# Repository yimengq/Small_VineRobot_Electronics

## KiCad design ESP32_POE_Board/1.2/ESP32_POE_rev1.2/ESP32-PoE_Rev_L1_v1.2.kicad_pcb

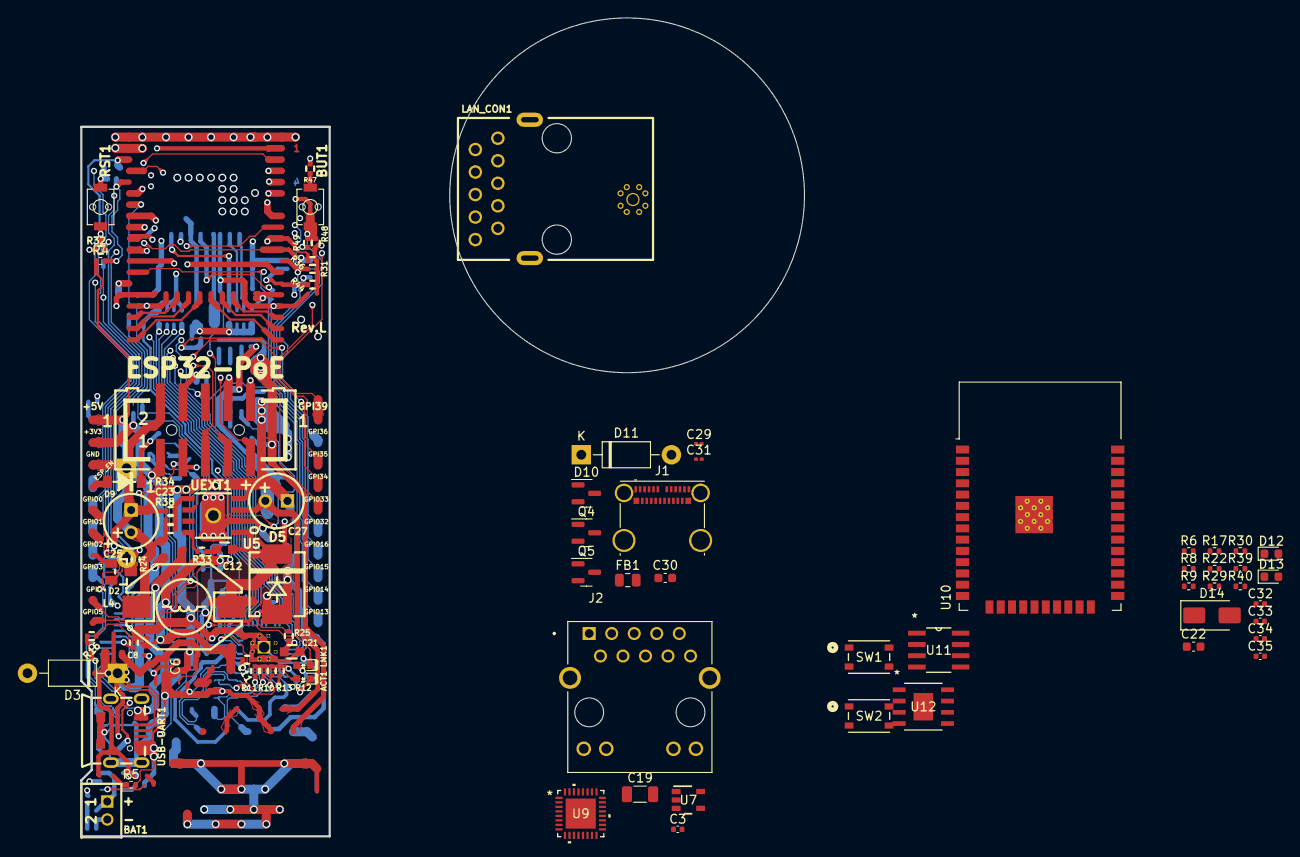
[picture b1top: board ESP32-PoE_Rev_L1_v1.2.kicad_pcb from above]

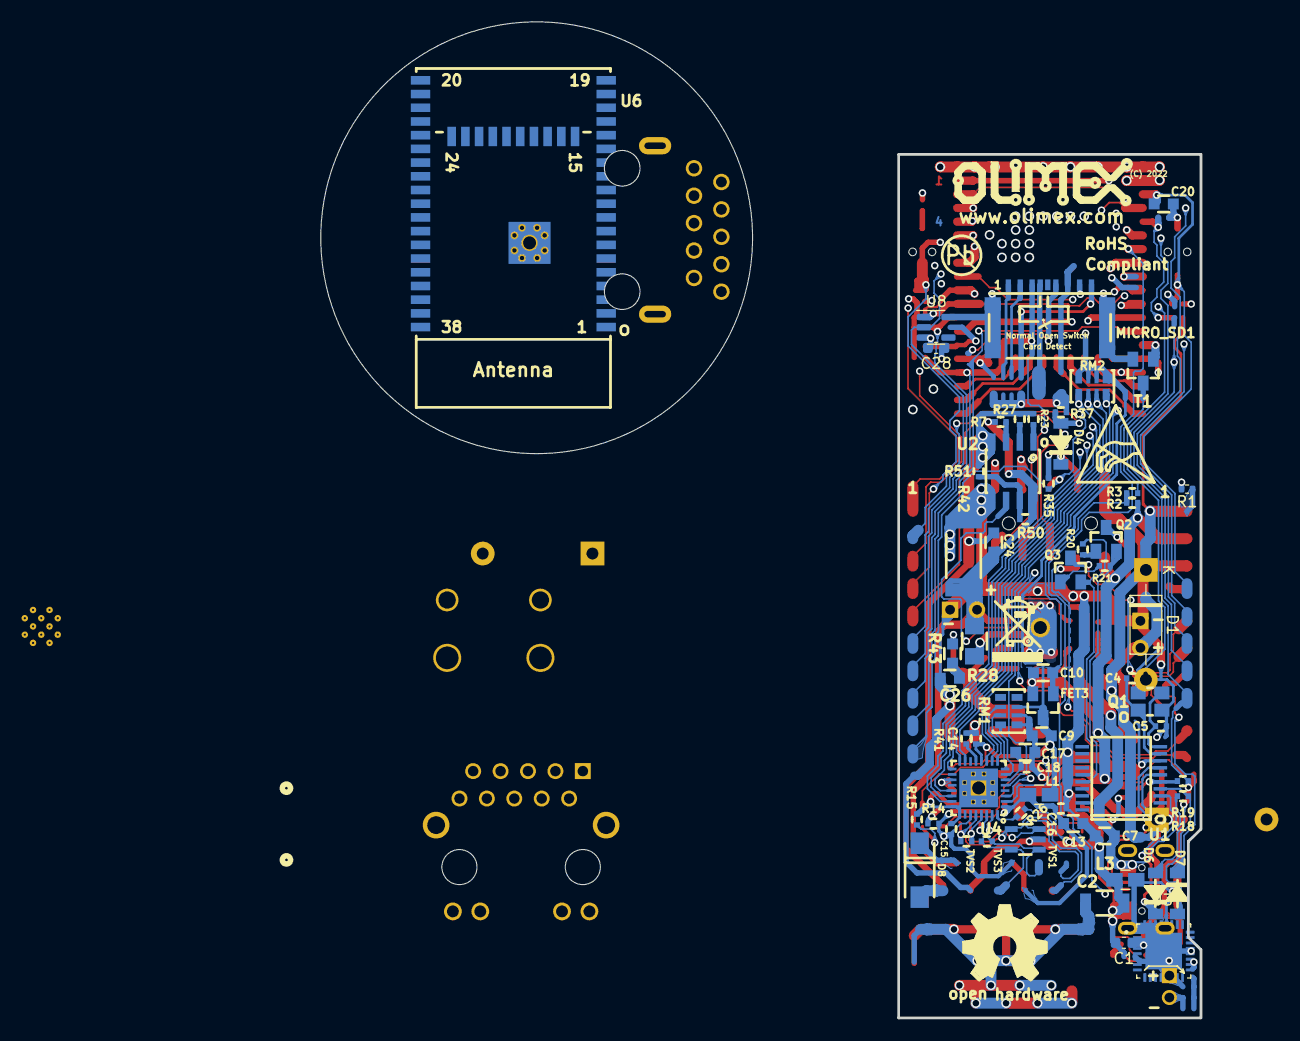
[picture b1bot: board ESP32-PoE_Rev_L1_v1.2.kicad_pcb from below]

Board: 4 copper layers, 81.5 x 92.3 mm, 144 parts (67 on the bottom side), 104 nets.

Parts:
ACT1: LED/YELLOW/0603; LED_0603_KA
BAT1: DW02S; LIPO_BAT_VERTICAL_DW02S
BUT1: IT1185AU2; IT1185AU2_V2
C1, C28, C30: 10uF; C_0603_1608Metric
C2: 1nF/2000V/10%/X7R/C1206; C_1206_5MIL_DWS_ISO
C3, C32, C34, C35: 100nF; C_0402_1005Metric
C4, C5: 27pF/50V/5%/C0G/C0402; C_0402_5MIL_DWS
C6, C29, C31: 1uF; C_0201_0603Metric
C7, C9, C10, C13: 22uF/6.3V/20%/X5R/C0603; C_0603_5MIL_DWS
C8, C11, C14, C15, C16, C18: 100nF/16V/10%/X7R/C0402; C_0402_5MIL_DWS
C12, C24: 100nF/100V/10%/X7R/C0603; C_0603_5MIL_DWS
C17: 2.2uF/6.3V/10%/X5R/C0603; C_0603_5MIL_DWS
C19: 1nF; C_1206_3216Metric
C20: 1uF/10V/20%/X5R/C0603; C_0603_5MIL_DWS
C21: NA(10uF/6.3V/20%/X5R/C0603); C_0603_5MIL_DWS
C22: 22uF; C_0603_1608Metric
C23: 12pF/50V/5%/COG/C0402; C_0402_5MIL_DWS
C25: 470uF/10V/20%/Low_ESR/RM2.5/6.0x11mm; CPOL-RM2.5mm_6.3x11mm_PTH
C26: NA(220pF/100V/C0603); C_0603_5MIL_DWS
C27: 15uF/100V/20%/RM2.5/6.3x11mm(Farnell:1281844); CPOL-RM2.5mm_6.3x11mm_PTH
C33: 2.2uF; C_0402_1005Metric
D1, D3, D11: 1N5819; D_DO-41_SOD81_P10.16mm_Horizontal
D2: BAT54C(SOT23-3); SOT23-3
D4, D6, D7, D9: 1N5819S4(SOD-123); SOD-123_1C-2A_KA
D5: SS510/100V/5A/0.85V/DO214AB(SMC); DO214AB(SMC)_1(K)-2(A)
D8: SMAJ58A/SMA; SMA-KA
D10: BAT54C; SOT-23
D12, D13: LED; LED_0603_1608Metric
D14: SMAJ58A; D_SMA
FB1: 600R-2A; C_0805_2012Metric
FET3: WPM2015-3/TR; SOT23
J1: USB_C_Receptacle; USB_C_Receptacle_Molex_105450-0101-L
J2: SI-46020-F; BEL_SI-46020-F
L1, L3: FB0805/600R/2A; L_0805_5MIL_DWS
L4: 33uH/2.1A/DCR=0.1R/20%/DBS135(PD3316MT330); DBS135
LAN_CON1: RJP-003TC1(LPJ4112CNL)
LNK1: LED/GREEN/0603; LED_0603_KA
Logo_OSHW: LOGO_OPENHARDWARE_8x8
Logo_Olimex: OLIMEX_LOGO_TB
MICRO_SD1: TFC-9P-1.7H(ATFFS150A01BR016); uSD(TFC-9P-1.xH(ATFFS150A01BR016))
Q1: Q12MHz/20pF/10ppm/4P/3.2x2.5mm; TSX-3.2x2.5mm_GND(3)
Q2, Q3: BC817-40(SOT23); SOT23
Q4, Q5: BC817; SOT-23
R1, R4: 1k; R_0402_1005Metric
R2, R18, R19, R25, R32, R36, R37, R48: 10k/R0402; R_0402_5MIL_DWS
R3, R20, R21: 1k/R0402; R_0402_5MIL_DWS
R5: 220; R_0402_1005Metric
R6, R8, R9, R17: 2.2k; R_0402_1005Metric
R7: 24.9k/1%/R0402; R_0402_5MIL_DWS
R10, R11, R12, R13: 49.9R/1%/R0402; R_0402_5MIL_DWS
R14, R15, R31, R35, R41: 2.2k/R0402; R_0402_5MIL_DWS
R16, R51: NA(10k/R0402); R_0402_5MIL_DWS
R22: 130k; R_0402_1005Metric
R23: 180k/1%/R0402; R_0402_5MIL_DWS
R24, R47: 220R/R0402; R_0402_5MIL_DWS
R26: 12.1k/1%/R0402; R_0402_5MIL_DWS
R27: 4.42k/1%/1/16W/R0402; R_0402_5MIL_DWS
R28: 0.03R/1%/R1206; R_1206_5MIL_DWS
R29, R30: 10k; R_0402_1005Metric
R33: 4.7R/R0402; R_0402_5MIL_DWS
R34: 5.23k/1%/R0402; R_0402_5MIL_DWS
R38: 30.1k/1%/R0402; R_0402_5MIL_DWS
R39: 4.42k; R_0402_1005Metric
R40: 24.9k; R_0402_1005Metric
R42: 4.7k/R2512; R_2512_MM_DWS
R43: NA(22R/R0603); R_0603_5MIL_DWS
R44, R49: NA/R0402; R_0402_5MIL_DWS
R50: NA(130k/R0402); R_0402_5MIL_DWS
RM1, RM2: RA1206_(4X0603)_4B8_2.2k; R_MATRIX_4
RST1: IT1185AU2; IT1185AU2_V2
SW1, SW2: PTS815 SJM 250 SMTR LFS; SW4_PTS815 SJM 250 SMTR LFS_CNK
Sign_Antistatic: Val**; LOGO_ANTISTATIC_1
Sign_PB-Free: LOGO_PBFREE
Sign_RecycleBin: LOGO_RECYCLEBIN_1
T1: LMUN2211LT1G(SOT-23); SOT23
TVS1: ESDS314DBVR(SOT-23-5); SOT-23-5
TVS2, TVS3: NA(GG0402052R542P); D_0402_5MIL_DWS
U1: CH340T(SSOP20W); SSOP-20W
U2: TPS2375D(SO-8); SOIC-8_1.75mm
U3: FT232RQ; QFN50P500X500X90-33N
U4: LAN8710A-EZC(QFN32); QFN32_EP(33)_5.00x5.00x0.90mm_Pitch_0.50mm
U5: TX4138(ESOIC-8); ESOIC-8
U6: ESP32-WROVER-E; ESP32-WROVER(WROOM)-UNIVERSAL_MODULE
U7: ESDS314DBVR; DBV0005A_N
U8: MIC5504-3.3YM5; SOT-23-5
U9: LAN8710A-EZC; QFN32_5X5MC_MCH
U10: ESP32-WROOM-32
U11: TPS2375D; D8
U12: TX4138; ESOIC8_XDS
UEXT1: P-B-V-10-LF; GBH-254-SMT-10
USB-UART1: MISB-SWMM-5B-LF(USB_MICRO); USB-MICRO_MISB-SWMM-5B_LF

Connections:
+3.3V: C10.1, C30.1, C31.1, FET3.2, R2.1, R16.2, R31.1, R32.1, R35.1, R36.1, R37.1, R44.2, R48.1, U6.2 (VDD33(3V3)), U8.5 (VOUT), UEXT1.1
+3.3VLAN: C9.1, C14.1, FET3.3, L1.1, R25.2, RM1.3.1, RM2.1.1, RM2.2.1, RM2.3.1, RM2.4.1, U4.12 (VDDIO)
+5VP: C23.1, C25.1 (+), C28.1, C29.1, L4.2, R38.1, U8.1 (VIN), U8.3 (EN)
/+5V_USB: C7.1, R18.1, U1.19 (VCC), USB-UART1.1 (VBUS)
/D_Com: D2.3 (CC), R24.2, R49.2
/GPI34\BUT1: BUT1.1, R48.2, R49.1, U6.6 (GPI34/ADC1_CH6/RTC_GPIO4)
/GPI36\U1RXD: D4.2 (A), R37.2, U6.4 (GPI36/SENSOR_VP/ADC1_CH0/RTC_GPIO0)
/GPIO1\U0TXD: D7.1 (K), U6.35 (GPIO1/U0TXD/CLK_OUT3/EMAC_RXD2)
/GPIO3\U0RXD: D6.2 (A), R16.1, R19.2, U6.34 (GPIO3/U0RXD/CLK_OUT2)
/GPIO4\U1TXD: U6.26 (GPIO4/ADC2_CH0/TOUCH0/RTC_GPIO10/HSPIHD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), UEXT1.3
/GPIO5\SPI_CS: R36.2, U6.29 (GPIO5/VSPICS0/HS1_DATA6/EMAC_RX_CLK), UEXT1.10
/GPIO12\PHY_PWR: T1.1 (B), U6.14 (GPIO12/ADC2_CH5/TOUCH5/RTC_GPIO15/MTDI/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)
/GPIO13\I2C-SDA: R35.2, U6.16 (GPIO13/ADC2_CH4/TOUCH4/RTC_GPIO14/MTCK/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), UEXT1.6
/GPIO14\HS2_CLK: U6.13 (GPIO14/ADC2_CH6/TOUCH6/RTC_GPIO16/MTMS/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), UEXT1.9
/GPIO15\HS2_CMD: MICRO_SD1.3 (CMD/DI), U6.23 (GPIO15/ADC2_CH3/TOUCH3/MTDO/HSPICS0/RTC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), UEXT1.7
/GPIO16\I2C-SCL: R31.2, U6.27 (NC(GPIO16/HS1_DATA4/U2RXD/EMAC_CLK_OUT)), UEXT1.5
/GPIO17\EMAC_CLK_OUT_180: U4.5 (XTAL1/CLKIN), U6.28 (NC(GPIO17/HS1_DATA5/U2TXD/EMAC_CLK_OUT_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)
/GPIO18\MDIO(RMII): RM2.4.2, U4.16 (MDIO), U6.30 (GPIO18/VSPICLK/HS1_DATA7)
/GPIO19\EMAC_TXD0(RMII): U4.22 (TXD0), U6.31 (GPIO19/VSPIQ/U0CTS/EMAC_TXD0)
/GPIO21\EMAC_TX_EN(RMII): U4.21 (TXEN), U6.33 (GPIO21/VSPIHD/EMAC_TX_EN)
/GPIO22\EMAC_TXD1(RMII): U4.23 (TXD1), U6.36 (GPIO22/VSPIWP/U0RTS/EMAC_TXD1)
/GPIO23\MDC(RMII): U4.17 (MDC), U6.37 (GPIO23/VSPID/HS1_STROBE)
/GPIO25\EMAC_RXD0(RMII): RM2.2.2, U4.11 (RXD0/MODE0), U6.10 (GPIO25/DAC_1/ADC2_CH8/RTC_GPIO6/EMAC_RX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)
/GPIO26\EMAC_RXD1(RMII): RM2.1.2, U4.10 (RXD1/MODE1), U6.11 (GPIO26/DAC_2/ADC2_CH9/RTC_GPIO7/EMAC_RX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)
/GPIO27\EMAC_RX_CRS_DV: RM2.3.2, U4.15 (COL/CRS_DV/MODE2), U6.12 (GPIO27/ADC2_CH7/TOUCH7/RTC_GPIO17/EMAC_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)
ESP_EN: C20.1, D9.2 (A), D11.2 (A), R32.2, RST1.1, U6.3 (EN)
GND: BAT1.2, C1.2, C2.1, C3.1, C4.2, C5.2, C6.2, C7.2, C8.2, C9.2, C11.2, C13.2, C14.2, C15.2, C16.2, C17.2, C18.2, C19.1, C20.2, C21.1, C22.2, C25.2 (-), C26.2, C27.2 (-), C28.2, C29.2, C30.2, C31.2, C32.2, C33.2, C34.2, D5.2 (A), FB1.2, J2.7, L3.2, LAN_CON1.7 (GND/NC), LAN_CON1.8 (NC/GND), MICRO_SD1.6 (GND), MICRO_SD1.CH1 (Card_Housing), Q1.3 (case), R8.2, R15.2, R26.2, R34.2, R41.1, R42.2, R47.2, RM1.1.1, RM1.2.1, RST1.2, T1.2 (E), TVS1.2 (GND), U1.8 (GND), U2.5 (RTN), U4.24 (TXD2), U4.25 (TXD3), U4.33 (GND), U5.4 (GND), U6.1 (GND), U6.15 (GND), U6.38 (GND), U6.39 (THERMAL_PAD), U7.2 (GND), U8.2 (GND), U11.5 (RTN), UEXT1.2, USB-UART1.5 (GND)
GPIO0: D2.2 (A2), D10.1, R44.1, U6.25 (GPIO0/ADC2_CH1/TOUCH1/RTC_GPIO11/CLK_OU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)
GPIO2\HS2_DATA0: D2.1 (A1), D10.2, U6.24 (GPIO2/ADC2_CH2/TOUCH2/RTC_GPIO12/HSPIWP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), UEXT1.8
GPIO18/MDIO(RMII): R17.2, U9.16 (MDIO)
GPIO27/EMAC_RX_CRS_DV: R9.2, U9.15 (COL/CRS_DV/*MODE2)
unnamed: ACT1.2 (A), U4.3 (LED1/REGOFF)
unnamed: ACT1.1 (K), R15.1
unnamed: BUT1.2, R47.1
unnamed: C10.2, FET3.1, R2.2, R3.1
unnamed: C12.2, R33.2
unnamed: C19.2, J2.S1 (SHIELD), J2.S2 (SHIELD)
unnamed: C26.1, R43.1
unnamed: D1.1 (K), U3.30 (TXD)
unnamed: D3.2 (A), U3.2 (RXD)
unnamed: D4.1 (K), UEXT1.4
unnamed: C12.1, D5.1 (K), L4.1, R43.2, U5.1 (SW)
unnamed: D6.1 (K), U1.3 (TXD)
unnamed: D7.2 (A), R18.2, U1.4 (RXD)
unnamed: D9.1 (K), Q2.3 (C)
unnamed: D10.3, R5.2
unnamed: D11.1 (K), Q4.3 (C)
unnamed: D12.2 (A), R6.1
unnamed: D12.1 (K), U9.2 (LED2/*NINTSEL)
unnamed: D13.2 (A), U9.3 (LED1/*REGOFF)
unnamed: D13.1 (K), R8.1
unnamed: L3.1, USB-UART1.0
unnamed: C11.1, C13.1, C15.1, C16.1, L1.2, LAN_CON1.4 (TCT), LAN_CON1.5 (RCT), R10.1, R11.1, R12.1, R13.1, R14.1, U4.1 (VDD2A), U4.27 (VDD1A)
unnamed: C2.2, LAN_CON1.0 (Shield)
unnamed: LNK1.2 (A), R14.2
unnamed: LNK1.1 (K), U4.2 (LED2/NINTSEL)
unnamed: Q2.1 (B), R20.2
unnamed: Q2.2 (E), R21.1, U1.16 (RTS#)
unnamed: Q3.1 (B), R21.2
unnamed: Q3.3 (C), R24.1
unnamed: Q3.2 (E), R20.1, U1.15 (DTR#)
unnamed: Q4.1 (B), R1.2
unnamed: Q4.2 (E), R4.1, U3.32 (~RTS)
unnamed: Q5.1 (B), R4.2
unnamed: Q5.3 (C), R1.1, U3.31 (~DTR)
unnamed: Q5.2 (E), R5.1
unnamed: R28.1, U5.2 (ILIM), U5.9 (ILIM)
unnamed: R3.2, T1.3 (C)
unnamed: U1.6 (UD+), USB-UART1.3 (D+)
unnamed: U1.7 (UD-), USB-UART1.2 (D-)
unnamed: C8.1, R19.1, U1.5 (V3)
unnamed: C4.1, Q1.1, U1.9 (XI)
unnamed: C5.1, Q1.2, U1.10 (XO)
unnamed: R27.2, U2.2 (CLASS)
unnamed: R7.2, U2.3 (DET)
unnamed: R23.1, U2.1 (ILIM)
unnamed: R50.2, R51.1, U2.7 (NC/UVLO)
unnamed: U2.6 (PG), U5.6 (EN)
unnamed: U3.4 (GND), U3.17 (GND), U3.20 (GND)
unnamed: J1.A7 (D-), J1.B7 (D-), U3.15 (USBDM)
unnamed: J1.A6 (D+), J1.B6 (D+), U3.14 (USBDP)
unnamed: C21.2, R25.1, U4.19 (NRST)
unnamed: R26.1, U4.32 (RBIAS)
unnamed: RM1.1.2, U4.7 (RXCLK/PHYAD1)
unnamed: RM1.3.2, U4.9 (RXD2/RMIISEL)
unnamed: RM1.2.2, U4.8 (RXD3/PHYAD2)
unnamed: R41.2, U4.13 (RXER/RXD4/PHYAD0)
unnamed: C17.1, C18.1, U4.6 (VDDCR)
unnamed: R33.1, U5.8 (BS)
unnamed: C23.2, R34.1, R38.2, U5.5 (FB)
unnamed: U10.1 (GND), U10.15 (GND), U10.38 (GND), U10.39 (GND)
unnamed: R39.2, U11.2 (CLASS)
unnamed: R40.2, U11.3 (DET)
unnamed: R30.2, U11.1 (ILIM)
unnamed: R22.2, R29.1, U11.7 (NC)
PW+: C35.1, D14.1 (A1), J2.9, R22.1, R40.1
PW-: C35.2, D14.2 (A2), J2.10, R29.2, R30.1, R39.1, U11.4 (VSS)
RCT: C1.1, C3.2, C6.1, C22.1, C32.1, C33.1, C34.1, FB1.1, J1.A1 (GND), J1.A4 (VBUS), J1.A9 (VBUS), J1.A12 (GND), J1.B1 (GND), J1.B4 (VBUS), J1.B9 (VBUS), J1.B12 (GND), J1.S1 (SHIELD), J2.2 (TCT), J2.5 (RCT), R6.2, R9.1, R17.1, U3.1 (VCCIO), U3.19 (VCC), U9.1 (VDD2A), U9.6 (VDDCR), U9.12 (VDDIO), U9.27 (VDD1A)
RD+: J2.4 (RD+), LAN_CON1.3 (RD+), R11.2, TVS1.1 (I/O1), TVS3.1 (IO1), U4.31 (RXP), U7.3 (I_O2)
RD-: J2.6 (RD-), LAN_CON1.6 (RD-), R10.2, TVS1.5 (I/O4), TVS3.2 (IO2), U4.30 (RXN), U7.5 (I_O4)
Spare1: C24.1, C27.1 (+), D8.1 (K), LAN_CON1.9 (PW+), R7.1, R28.2, R42.1, R50.1, U2.8 (VDD), U5.3 (Vin)
Spare2: C24.2, D8.2 (A), LAN_CON1.10 (PW-), R23.2, R27.1, R51.2, U2.4 (VSS)
TD+: J2.1 (TD+), LAN_CON1.1 (TD+), R13.2, TVS1.3 (I/O2), TVS2.2 (IO2), U4.29 (TXP), U7.1 (I_O1)
TD-: J2.3 (TD-), LAN_CON1.2 (TD-), R12.2, TVS1.4 (I/O3), TVS2.1 (IO1), U4.28 (TXN), U7.4 (I_O3)

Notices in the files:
ESP32_POE_Board/1.2/ESP32_POE_rev1.2/ESP32-PoE_Rev_L1_v1.2.kicad_pcb:
(C) 2022
